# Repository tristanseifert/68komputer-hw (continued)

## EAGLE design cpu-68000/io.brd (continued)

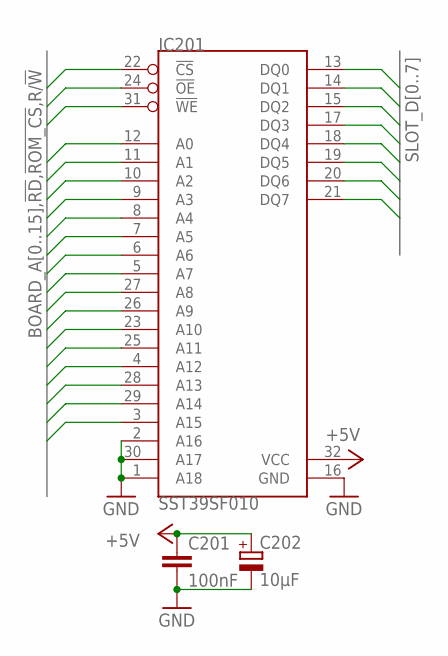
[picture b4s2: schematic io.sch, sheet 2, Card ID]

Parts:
C201: 100nF; C0805; MOUSER 710-885012207072
C202: 10µF; SMC_B; MOUSER 581-TAJB106K020RNJV
IC201: SST39SF010; PLCC-S32; MOUSER 579-SST3910A554INHET

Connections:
!RD: IC201.24 (!OE); also elsewhere on the board
!ROM_CS: IC201.22 (!CS); also elsewhere on the board
+5V: C201.1, C202.+, IC201.32 (VCC); also elsewhere on the board
BOARD_A0: IC201.12 (A0); also elsewhere on the board
BOARD_A1: IC201.11 (A1); also elsewhere on the board
BOARD_A2: IC201.10 (A2); also elsewhere on the board
BOARD_A3: IC201.9 (A3); also elsewhere on the board
BOARD_A4: IC201.8 (A4); also elsewhere on the board
BOARD_A5: IC201.7 (A5); also elsewhere on the board
BOARD_A6: IC201.6 (A6); also elsewhere on the board
BOARD_A7: IC201.5 (A7); also elsewhere on the board
BOARD_A8: IC201.27 (A8); also elsewhere on the board
BOARD_A9: IC201.26 (A9); also elsewhere on the board
BOARD_A10: IC201.23 (A10); also elsewhere on the board
BOARD_A11: IC201.25 (A11); also elsewhere on the board
BOARD_A12: IC201.4 (A12); also elsewhere on the board
BOARD_A13: IC201.28 (A13); also elsewhere on the board
BOARD_A14: IC201.29 (A14); also elsewhere on the board
BOARD_A15: IC201.3 (A15); also elsewhere on the board
GND: C201.2, C202.-, IC201.1 (A18), IC201.2 (A16), IC201.16 (GND), IC201.30 (A17); also elsewhere on the board
R/!W!: IC201.31 (!WE); also elsewhere on the board
SLOT_D0: IC201.13 (DQ0); also elsewhere on the board
SLOT_D1: IC201.14 (DQ1); also elsewhere on the board
SLOT_D2: IC201.15 (DQ2); also elsewhere on the board
SLOT_D3: IC201.17 (DQ3); also elsewhere on the board
SLOT_D4: IC201.18 (DQ4); also elsewhere on the board
SLOT_D5: IC201.19 (DQ5); also elsewhere on the board
SLOT_D6: IC201.20 (DQ6); also elsewhere on the board
SLOT_D7: IC201.21 (DQ7); also elsewhere on the board

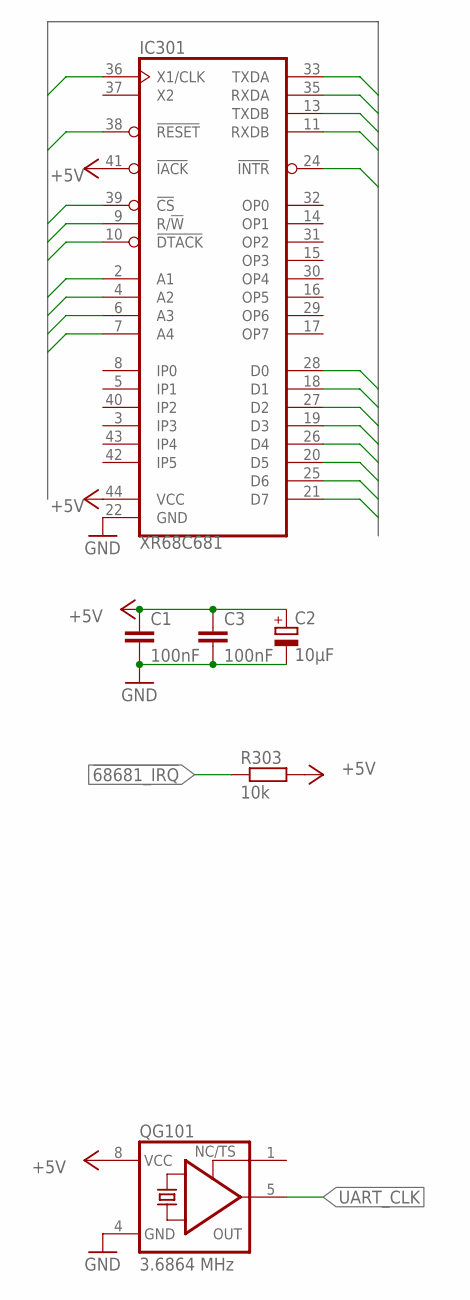
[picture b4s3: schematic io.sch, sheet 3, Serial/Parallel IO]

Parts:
C1, C3: 100nF; C0805; MOUSER 710-885012207072
C2: 10µF; SMC_B; MOUSER 581-TAJB106K020RNJV
IC301: XR68C681; PLCC-S44; MOUSER 701-XR68C681CJ-F
QG101: 3.6864 MHz; DIL08S; MOUSER 774-MXO45HS-3C-3.6
R303: 10k; R2012; MOUSER 652-CR0805FX-1002ELF

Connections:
!68681_IRQ: IC301.24 (!INTR), R303.1
!DTACK: IC301.10 (!DTACK); also elsewhere on the board
!DUART_CS: IC301.39 (!CS); also elsewhere on the board
!LWE: IC301.9 (R/!W)
!RESET: IC301.38 (!RESET); also elsewhere on the board
+5V: C1.1, C2.+, C3.1, IC301.41 (!IACK), IC301.44 (VCC), QG101.8 (VCC), R303.2; also elsewhere on the board
A_RX: IC301.35 (RXDA)
A_TX: IC301.33 (TXDA)
BOARD_A0: IC301.2 (A1); also elsewhere on the board
BOARD_A1: IC301.4 (A2); also elsewhere on the board
BOARD_A2: IC301.6 (A3); also elsewhere on the board
BOARD_A3: IC301.7 (A4); also elsewhere on the board
BOARD_D0: IC301.28 (D0); also elsewhere on the board
BOARD_D1: IC301.18 (D1); also elsewhere on the board
BOARD_D2: IC301.27 (D2); also elsewhere on the board
BOARD_D3: IC301.19 (D3); also elsewhere on the board
BOARD_D4: IC301.26 (D4); also elsewhere on the board
BOARD_D5: IC301.20 (D5); also elsewhere on the board
BOARD_D6: IC301.25 (D6); also elsewhere on the board
BOARD_D7: IC301.21 (D7); also elsewhere on the board
B_RX: IC301.11 (RXDB)
B_TX: IC301.13 (TXDB)
GND: C1.2, C2.-, C3.2, IC301.22 (GND), QG101.4 (GND); also elsewhere on the board
UART_CLK: IC301.36 (X1/CLK), QG101.5 (OUT); also elsewhere on the board

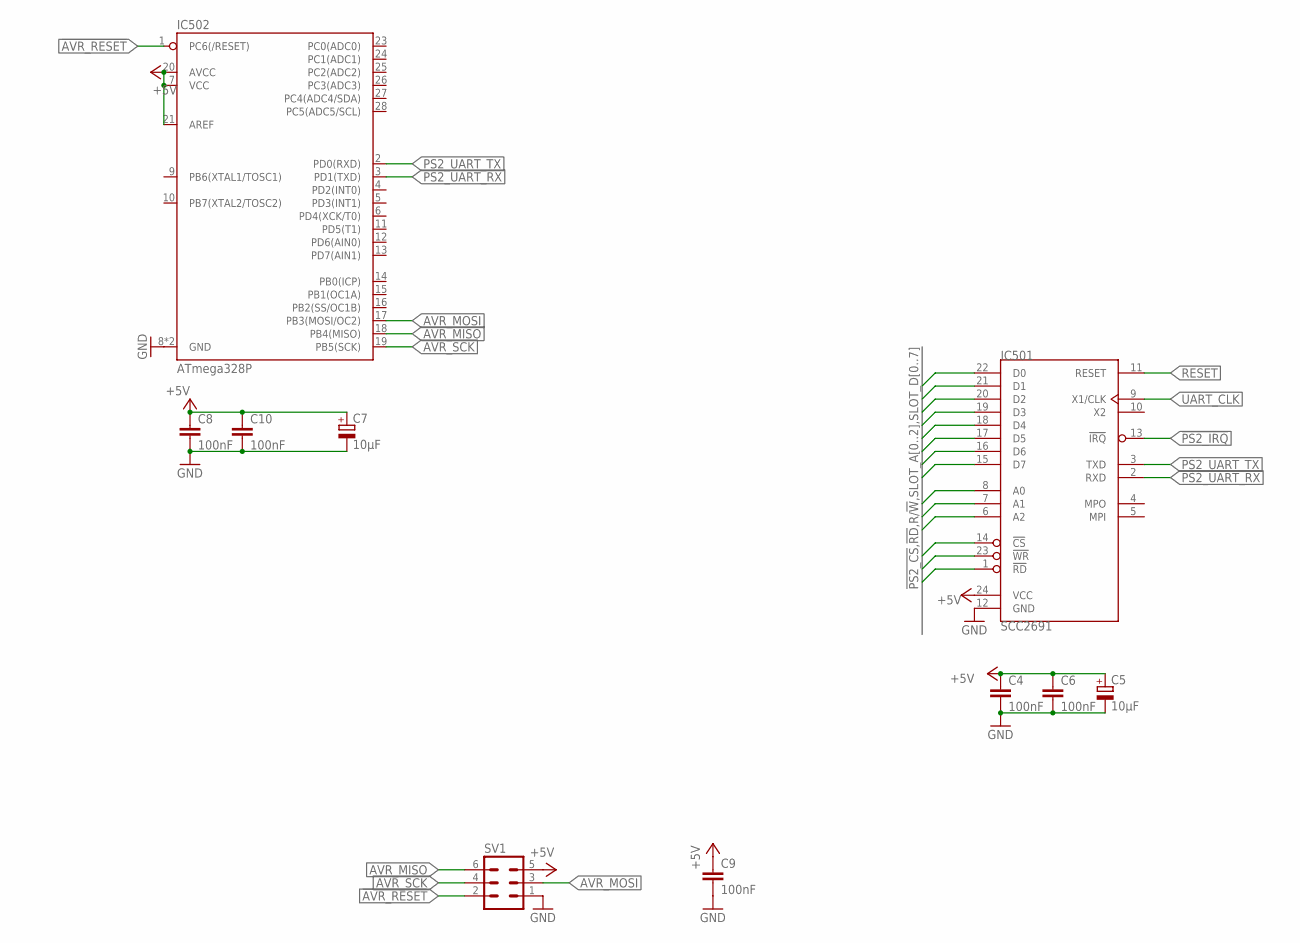
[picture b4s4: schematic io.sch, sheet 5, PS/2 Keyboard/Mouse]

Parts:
C4, C6, C8, C9, C10: 100nF; C0805; MOUSER 710-885012207072
C5, C7: 10µF; SMC_B; MOUSER 581-TAJB106K020RNJV
IC501: SCC2691; DIL24S; MOUSER_SOCKET 575-1104732441001000
IC502: ATmega328P; DIP28; MOUSER 556-ATMEGA328-PU
SV1: ML6

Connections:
!AVR_RESET: IC502.1 (PC6(/RESET)), SV1.2
!PS2_CS: IC501.14 (!CS); also elsewhere on the board
!PS2_IRQ: IC501.13 (!IRQ)
!RD: IC501.1 (!RD); also elsewhere on the board
+5V: C4.1, C5.+, C6.1, C7.+, C8.1, C9.1, C10.1, IC501.24 (VCC), IC502.7 (VCC), IC502.20 (AVCC), IC502.21 (AREF), SV1.5; also elsewhere on the board
AVR_MISO: IC502.18 (PB4(MISO)), SV1.6
AVR_MOSI: IC502.17 (PB3(MOSI/OC2)), SV1.3
AVR_SCK: IC502.19 (PB5(SCK)), SV1.4
GND: C4.2, C5.-, C6.2, C7.-, C8.2, C9.2, C10.2, IC501.12 (GND), IC502.8 (GND), IC502.22 (GND), SV1.1; also elsewhere on the board
PS2_UART_RX: IC501.2 (RXD), IC502.3 (PD1(TXD))
PS2_UART_TX: IC501.3 (TXD), IC502.2 (PD0(RXD))
R/!W!: IC501.23 (!WR); also elsewhere on the board
RESET: IC501.11 (RESET)
SLOT_A0: IC501.8 (A0)
SLOT_A1: IC501.7 (A1)
SLOT_A2: IC501.6 (A2)
SLOT_D0: IC501.22 (D0); also elsewhere on the board
SLOT_D1: IC501.21 (D1); also elsewhere on the board
SLOT_D2: IC501.20 (D2); also elsewhere on the board
SLOT_D3: IC501.19 (D3); also elsewhere on the board
SLOT_D4: IC501.18 (D4); also elsewhere on the board
SLOT_D5: IC501.17 (D5); also elsewhere on the board
SLOT_D6: IC501.16 (D6); also elsewhere on the board
SLOT_D7: IC501.15 (D7); also elsewhere on the board
UART_CLK: IC501.9 (X1/CLK); also elsewhere on the board

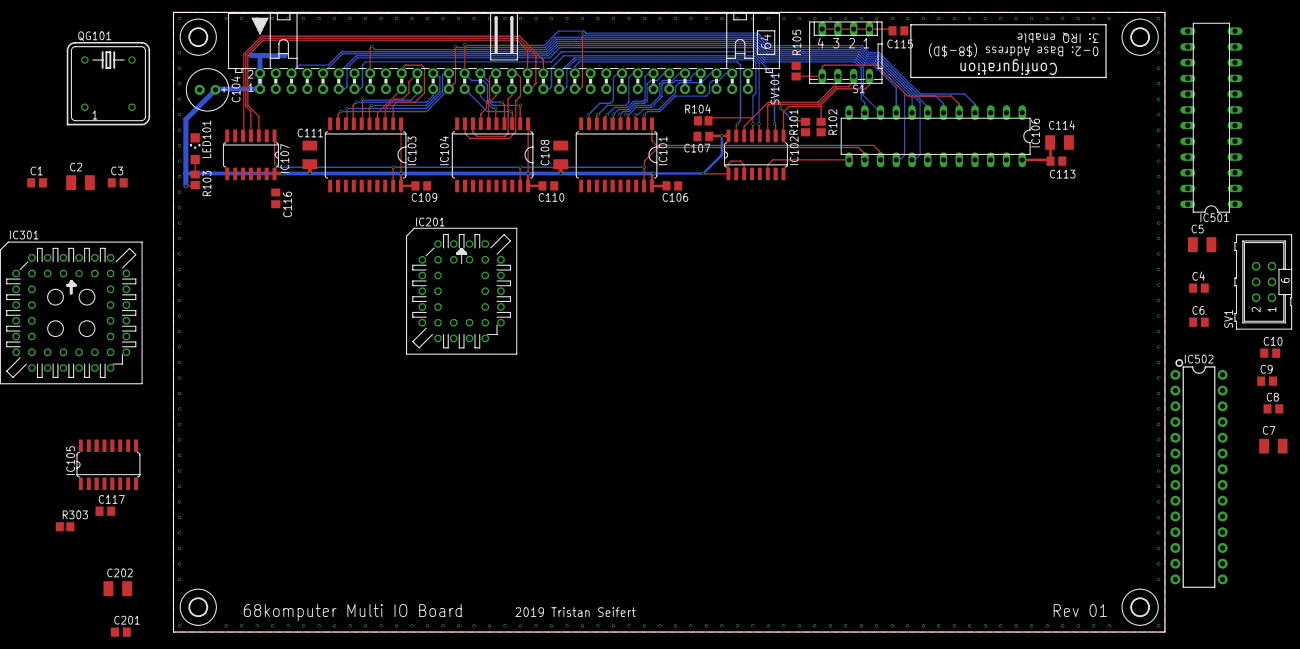
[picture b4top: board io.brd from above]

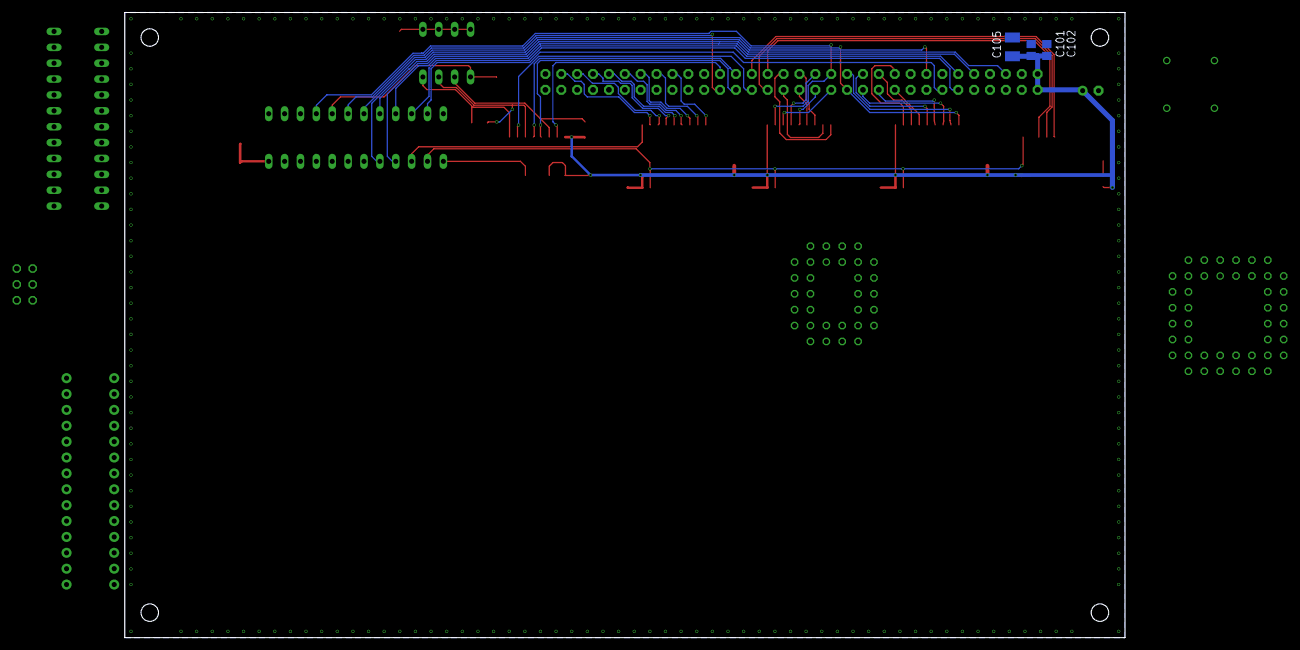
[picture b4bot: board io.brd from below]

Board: 2 copper layers, 160.0 x 100.0 mm, 53 parts (3 on the bottom side), 92 nets.

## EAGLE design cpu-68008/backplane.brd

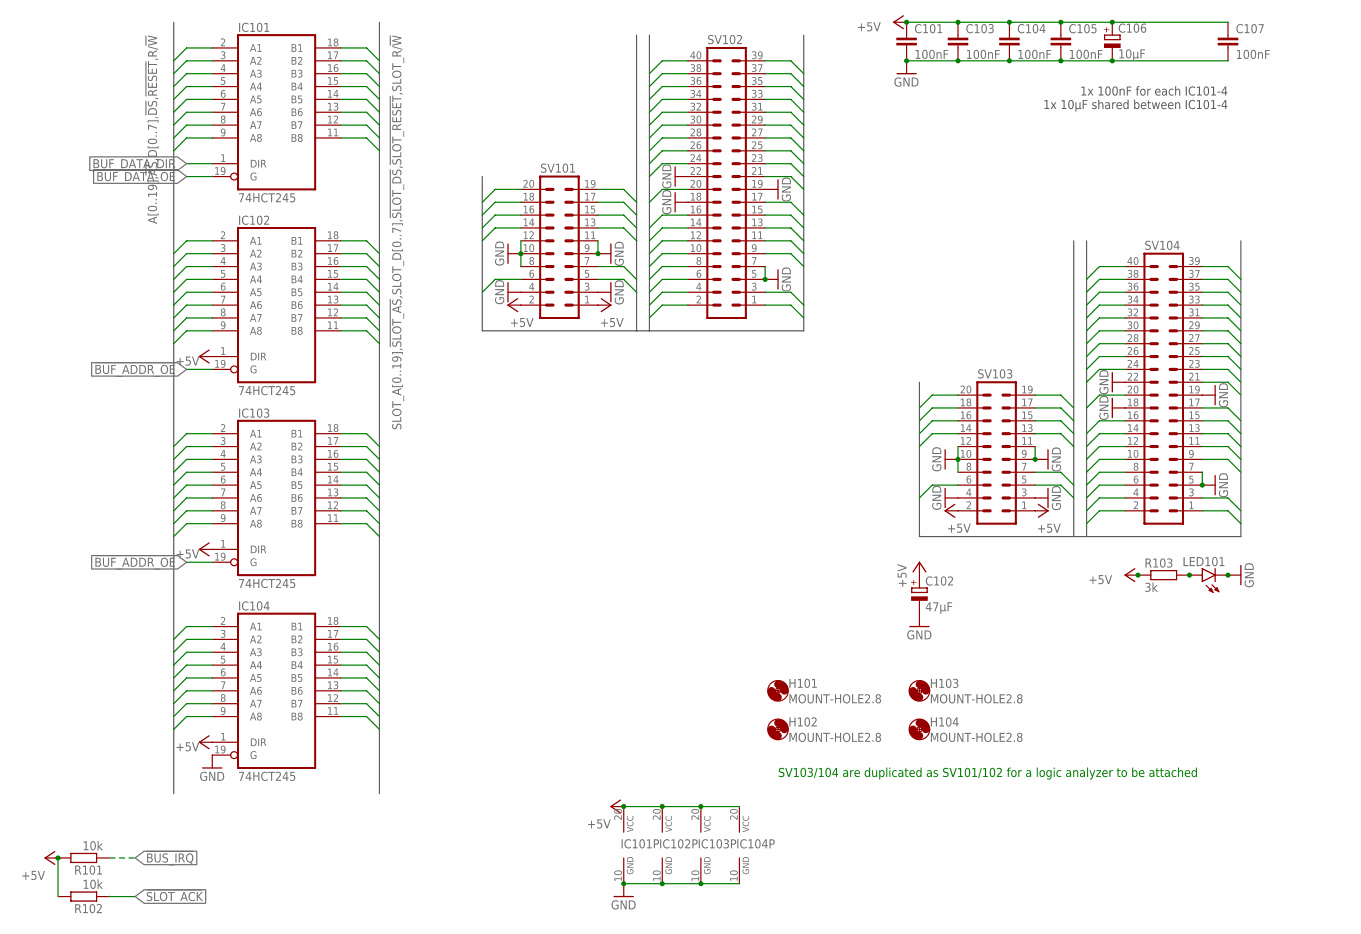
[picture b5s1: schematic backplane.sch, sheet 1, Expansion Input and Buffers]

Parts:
C101, C103, C104, C105, C107: 100nF; C0805; MOUSER 710-885012207072
C102: 47µF; E2-5; MOUSER 710-860020472006
C106: 10µF; SMC_B; MOUSER 581-TAJB106K020RNJV
H101, H102, H103, H104: MOUNT-HOLE2.8; 2,8
IC101, IC102, IC103, IC104: 74HCT245; SO20W
LED101: LEDCHIPLED_1206; CHIPLED_1206; MOUSER 710-156120YS75300
R101, R102: 10k; R2012; MOUSER 652-CR0805FX-1002ELF
R103: 3k; R2012; MOUSER 652-CR0805JW-302ELF
SV101: MA10-2
SV102: MA20-2
SV103: MA10-2W
SV104: MA20-2W

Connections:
!AS: IC104.2 (A1), SV102.33, SV104.33
!BERR: SV102.9, SV104.9
!BG: SV102.25, SV104.25
!BR: SV102.23, SV104.23
!BUF_ADDR_OE: IC102.19 (G), IC103.19 (G); also elsewhere on the board
!BUF_DATA_OE: IC101.19 (G); also elsewhere on the board
!BUS_CS: SV101.7, SV103.7; also elsewhere on the board
!BUS_DTACK: SV101.6, SV103.6; also elsewhere on the board
!BUS_IRQ: R101.1, SV101.5, SV103.5; also elsewhere on the board
!DS: IC104.3 (A2), SV102.31, SV104.31
!DTACK: SV102.27, SV104.27
!HALT: SV102.17, SV104.17
!RESET: IC104.9 (A8), SV102.15, SV104.15
!SLOT_ACK: R102.1; also elsewhere on the board
!SLOT_AS: IC104.18 (B1); also elsewhere on the board
!SLOT_RESET: IC104.11 (B8); also elsewhere on the board
!VPA: SV102.11, SV104.11
+5V: C101.1, C102.+, C103.1, C104.1, C105.1, C106.+, C107.1, IC101.20 (VCC), IC102.1 (DIR), IC102.20 (VCC), IC103.1 (DIR), IC103.20 (VCC), IC104.1 (DIR), IC104.20 (VCC), R101.2, R102.2, R103.1, SV101.1, SV101.2, SV103.1, SV103.2; also elsewhere on the board
A0: IC102.5 (A4), SV101.17, SV103.17
A1: IC102.7 (A6), SV101.15, SV103.15
A2: IC102.9 (A8), SV101.13, SV103.13
A3: IC102.8 (A7), SV101.14, SV103.14
A4: IC102.6 (A5), SV101.16, SV103.16
A5: IC102.4 (A3), SV101.18, SV103.18
A6: IC102.3 (A2), SV101.20, SV103.20
A7: IC102.2 (A1), SV102.2, SV104.2
A8: IC103.9 (A8), SV102.4, SV104.4
A9: IC103.8 (A7), SV102.6, SV104.6
A10: IC103.7 (A6), SV102.8, SV104.8
A11: IC103.6 (A5), SV102.10, SV104.10
A12: IC103.5 (A4), SV102.12, SV104.12
A13: IC103.4 (A3), SV102.14, SV104.14
A14: IC103.3 (A2), SV102.16, SV104.16
A15: IC103.2 (A1), SV102.20, SV104.20
A16: IC104.8 (A7), SV102.24, SV104.24
A17: IC104.7 (A6), SV102.26, SV104.26
A18: IC104.6 (A5), SV102.28, SV104.28
A19: IC104.4 (A3), SV102.30, SV104.30
BUF_DATA_DIR: IC101.1 (DIR); also elsewhere on the board
CLK: SV102.21, SV104.21; also elsewhere on the board
D0: IC101.7 (A6), SV102.35, SV104.35
D1: IC101.5 (A4), SV102.37, SV104.37
D2: IC101.3 (A2), SV102.39, SV104.39
D3: IC101.2 (A1), SV102.40, SV104.40
D4: IC101.4 (A3), SV102.38, SV104.38
D5: IC101.6 (A5), SV102.36, SV104.36
D6: IC101.8 (A7), SV102.34, SV104.34
D7: IC101.9 (A8), SV102.32, SV104.32
E: SV102.13, SV104.13
FC0: SV101.19, SV103.19
FC1: SV102.1, SV104.1
FC2: SV102.3, SV104.3
GND: C101.2, C102.-, C103.2, C104.2, C105.2, C106.-, C107.2, IC101.10 (GND), IC102.10 (GND), IC103.10 (GND), IC104.10 (GND), IC104.19 (G), LED101.C, SV101.3, SV101.4, SV101.8, SV101.9, SV101.10, SV101.11, SV101.12, SV102.5, SV102.7, SV102.18, SV102.19, SV102.22, SV103.3, SV103.4, SV103.8, SV103.9, SV103.10, SV103.11, SV103.12, SV104.5, SV104.7, SV104.18, SV104.19, SV104.22; also elsewhere on the board
unnamed: LED101.A, R103.2
R/!W!: IC104.5 (A4), SV102.29, SV104.29
SLOT_A0: IC102.15 (B4); also elsewhere on the board
SLOT_A1: IC102.13 (B6); also elsewhere on the board
SLOT_A2: IC102.11 (B8); also elsewhere on the board
SLOT_A3: IC102.12 (B7); also elsewhere on the board
SLOT_A4: IC102.14 (B5); also elsewhere on the board
SLOT_A5: IC102.16 (B3); also elsewhere on the board
SLOT_A6: IC102.17 (B2); also elsewhere on the board
SLOT_A7: IC102.18 (B1); also elsewhere on the board
SLOT_A8: IC103.11 (B8); also elsewhere on the board
SLOT_A9: IC103.12 (B7); also elsewhere on the board
SLOT_A10: IC103.13 (B6); also elsewhere on the board
SLOT_A11: IC103.14 (B5); also elsewhere on the board
SLOT_A12: IC103.15 (B4); also elsewhere on the board
SLOT_A13: IC103.16 (B3); also elsewhere on the board
SLOT_A14: IC103.17 (B2); also elsewhere on the board
SLOT_A15: IC103.18 (B1); also elsewhere on the board
SLOT_A16: IC104.12 (B7); also elsewhere on the board
SLOT_A17: IC104.13 (B6); also elsewhere on the board
SLOT_A18: IC104.14 (B5); also elsewhere on the board
SLOT_A19: IC104.16 (B3); also elsewhere on the board
SLOT_D0: IC101.13 (B6); also elsewhere on the board
SLOT_D1: IC101.15 (B4); also elsewhere on the board
SLOT_D2: IC101.17 (B2); also elsewhere on the board
SLOT_D3: IC101.18 (B1); also elsewhere on the board
SLOT_D4: IC101.16 (B3); also elsewhere on the board
SLOT_D5: IC101.14 (B5); also elsewhere on the board
SLOT_D6: IC101.12 (B7); also elsewhere on the board
SLOT_D7: IC101.11 (B8); also elsewhere on the board
SLOT_R/!W!: IC104.15 (B4); also elsewhere on the board

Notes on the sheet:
1x 100nF for each IC101-4 1x 10µF shared between IC101-4
SV103/104 are duplicated as SV101/102 for a logic analyzer to be attached

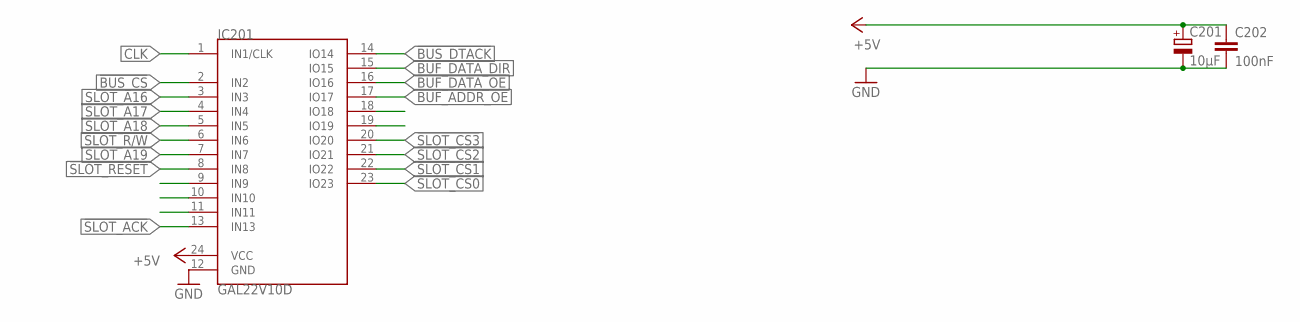
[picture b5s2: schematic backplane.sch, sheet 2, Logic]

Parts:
C201: 10µF; SMC_B; MOUSER 581-TAJB106K020RNJV
C202: 100nF; C0805; MOUSER 710-885012207072
IC201: GAL22V10D; DIL24S

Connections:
!BUF_ADDR_OE: IC201.17 (IO17); also elsewhere on the board
!BUF_DATA_OE: IC201.16 (IO16); also elsewhere on the board
!BUS_CS: IC201.2 (IN2); also elsewhere on the board
!BUS_DTACK: IC201.14 (IO14); also elsewhere on the board
!SLOT_ACK: IC201.13 (IN13); also elsewhere on the board
!SLOT_CS0: IC201.23 (IO23); also elsewhere on the board
!SLOT_CS1: IC201.22 (IO22); also elsewhere on the board
!SLOT_CS2: IC201.21 (IO21); also elsewhere on the board
!SLOT_CS3: IC201.20 (IO20); also elsewhere on the board
!SLOT_RESET: IC201.8 (IN8); also elsewhere on the board
+5V: C201.+, C202.1, IC201.24 (VCC); also elsewhere on the board
BUF_DATA_DIR: IC201.15 (IO15); also elsewhere on the board
CLK: IC201.1 (IN1/CLK); also elsewhere on the board
GND: C201.-, C202.2, IC201.12 (GND); also elsewhere on the board
SLOT_A16: IC201.3 (IN3); also elsewhere on the board
SLOT_A17: IC201.4 (IN4); also elsewhere on the board
SLOT_A18: IC201.5 (IN5); also elsewhere on the board
SLOT_A19: IC201.7 (IN7); also elsewhere on the board
SLOT_R/!W!: IC201.6 (IN6); also elsewhere on the board

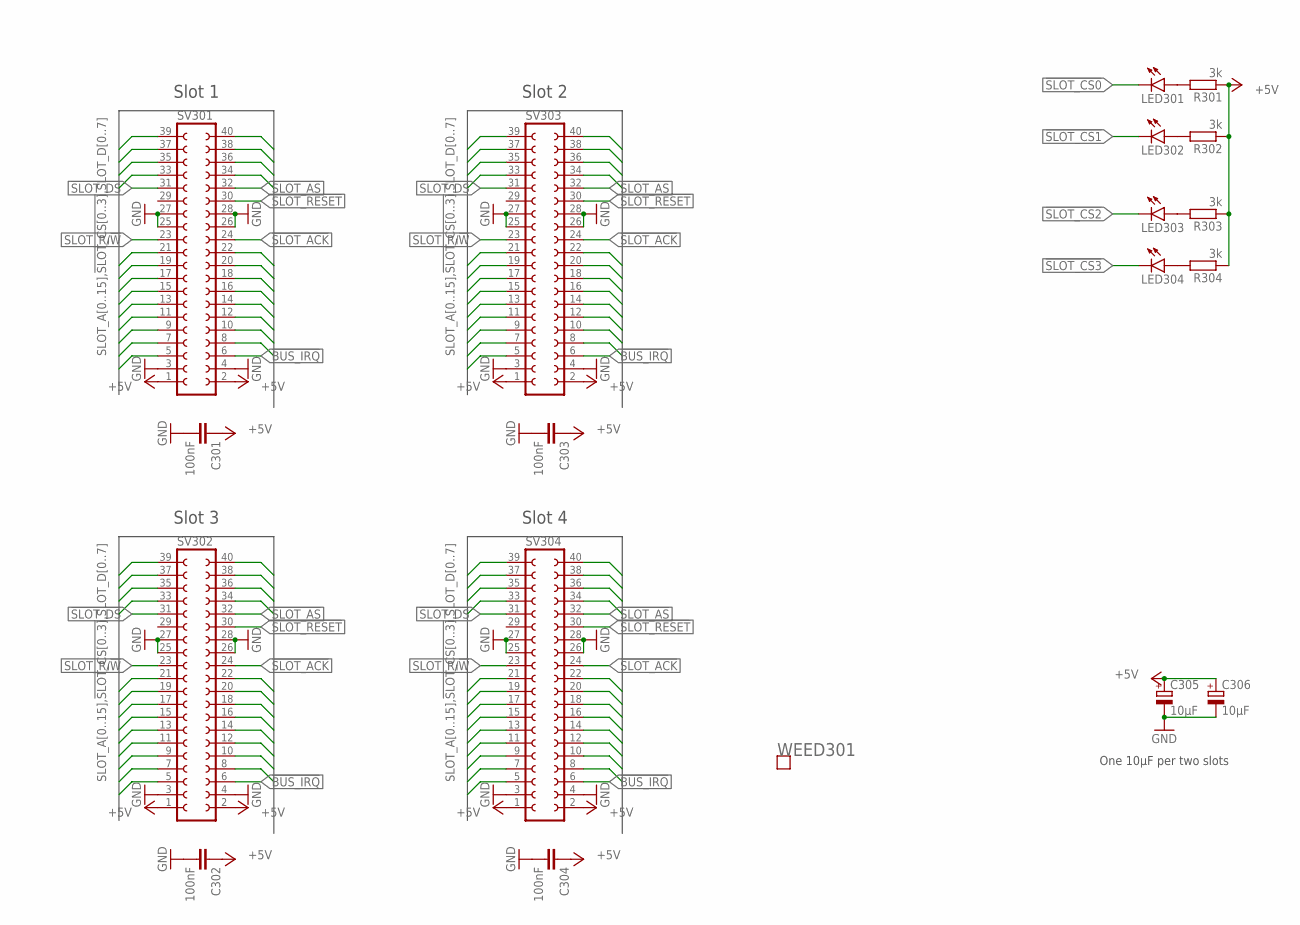
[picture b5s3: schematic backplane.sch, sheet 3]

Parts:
C301, C302, C303, C304: 100nF; C0805; MOUSER 710-885012207072
C305, C306: 10µF; SMC_B; MOUSER 581-TAJB106K020RNJV
LED301, LED302, LED303, LED304: LEDCHIPLED_1206; CHIPLED_1206; MOUSER 710-156120VS75300
R301, R302, R303, R304: 3k; R2012; MOUSER 652-CR0805JW-302ELF
SV301, SV302, SV303, SV304: FE20-2
WEED301: WEED; DOINK

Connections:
!BUS_IRQ: SV301.6, SV302.6, SV303.6, SV304.6; also elsewhere on the board
!SLOT_ACK: SV301.24, SV302.24, SV303.24, SV304.24; also elsewhere on the board
!SLOT_AS: SV301.32, SV302.32, SV303.32, SV304.32; also elsewhere on the board
!SLOT_CS0: LED301.C, SV301.5; also elsewhere on the board
!SLOT_CS1: LED302.C, SV303.5; also elsewhere on the board
!SLOT_CS2: LED303.C, SV302.5; also elsewhere on the board
!SLOT_CS3: LED304.C, SV304.5; also elsewhere on the board
!SLOT_RESET: SV301.30, SV302.30, SV303.30, SV304.30; also elsewhere on the board
+5V: C301.1, C302.1, C303.1, C304.1, C305.+, C306.+, R301.1, R302.1, R303.1, R304.1, SV301.1, SV301.2, SV302.1, SV302.2, SV303.1, SV303.2, SV304.1, SV304.2; also elsewhere on the board
GND: C301.2, C302.2, C303.2, C304.2, C305.-, C306.-, SV301.3, SV301.4, SV301.25, SV301.26, SV301.27, SV301.28, SV302.3, SV302.4, SV302.25, SV302.26, SV302.27, SV302.28, SV303.3, SV303.4, SV303.25, SV303.26, SV303.27, SV303.28, SV304.3, SV304.4, SV304.25, SV304.26, SV304.27, SV304.28; also elsewhere on the board
unnamed: LED302.A, R302.2
unnamed: LED301.A, R301.2
unnamed: LED304.A, R304.2
unnamed: LED303.A, R303.2
SLOT_A0: SV301.12, SV302.12, SV303.12, SV304.12; also elsewhere on the board
SLOT_A1: SV301.10, SV302.10, SV303.10, SV304.10; also elsewhere on the board
SLOT_A2: SV301.8, SV302.8, SV303.8, SV304.8; also elsewhere on the board
SLOT_A3: SV301.7, SV302.7, SV303.7, SV304.7; also elsewhere on the board
SLOT_A4: SV301.9, SV302.9, SV303.9, SV304.9; also elsewhere on the board
SLOT_A5: SV301.11, SV302.11, SV303.11, SV304.11; also elsewhere on the board
SLOT_A6: SV301.14, SV302.14, SV303.14, SV304.14; also elsewhere on the board
SLOT_A7: SV301.13, SV302.13, SV303.13, SV304.13; also elsewhere on the board
SLOT_A8: SV301.16, SV302.16, SV303.16, SV304.16; also elsewhere on the board
SLOT_A9: SV301.15, SV302.15, SV303.15, SV304.15; also elsewhere on the board
SLOT_A10: SV301.18, SV302.18, SV303.18, SV304.18; also elsewhere on the board
SLOT_A11: SV301.17, SV302.17, SV303.17, SV304.17; also elsewhere on the board
SLOT_A12: SV301.20, SV302.20, SV303.20, SV304.20; also elsewhere on the board
SLOT_A13: SV301.19, SV302.19, SV303.19, SV304.19; also elsewhere on the board
SLOT_A14: SV301.22, SV302.22, SV303.22, SV304.22; also elsewhere on the board
SLOT_A15: SV301.21, SV302.21, SV303.21, SV304.21; also elsewhere on the board
SLOT_D0: SV301.35, SV302.35, SV303.35, SV304.35; also elsewhere on the board
SLOT_D1: SV301.37, SV302.37, SV303.37, SV304.37; also elsewhere on the board
SLOT_D2: SV301.39, SV302.39, SV303.39, SV304.39; also elsewhere on the board
SLOT_D3: SV301.40, SV302.40, SV303.40, SV304.40; also elsewhere on the board
SLOT_D4: SV301.38, SV302.38, SV303.38, SV304.38; also elsewhere on the board
SLOT_D5: SV301.36, SV302.36, SV303.36, SV304.36; also elsewhere on the board
SLOT_D6: SV301.34, SV302.34, SV303.34, SV304.34; also elsewhere on the board
SLOT_D7: SV301.33, SV302.33, SV303.33, SV304.33; also elsewhere on the board
SLOT_R/!W!: SV301.23, SV302.23, SV303.23, SV304.23; also elsewhere on the board

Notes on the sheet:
Slot 1
Slot 2
Slot 3
Slot 4
One 10µF per two slots

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
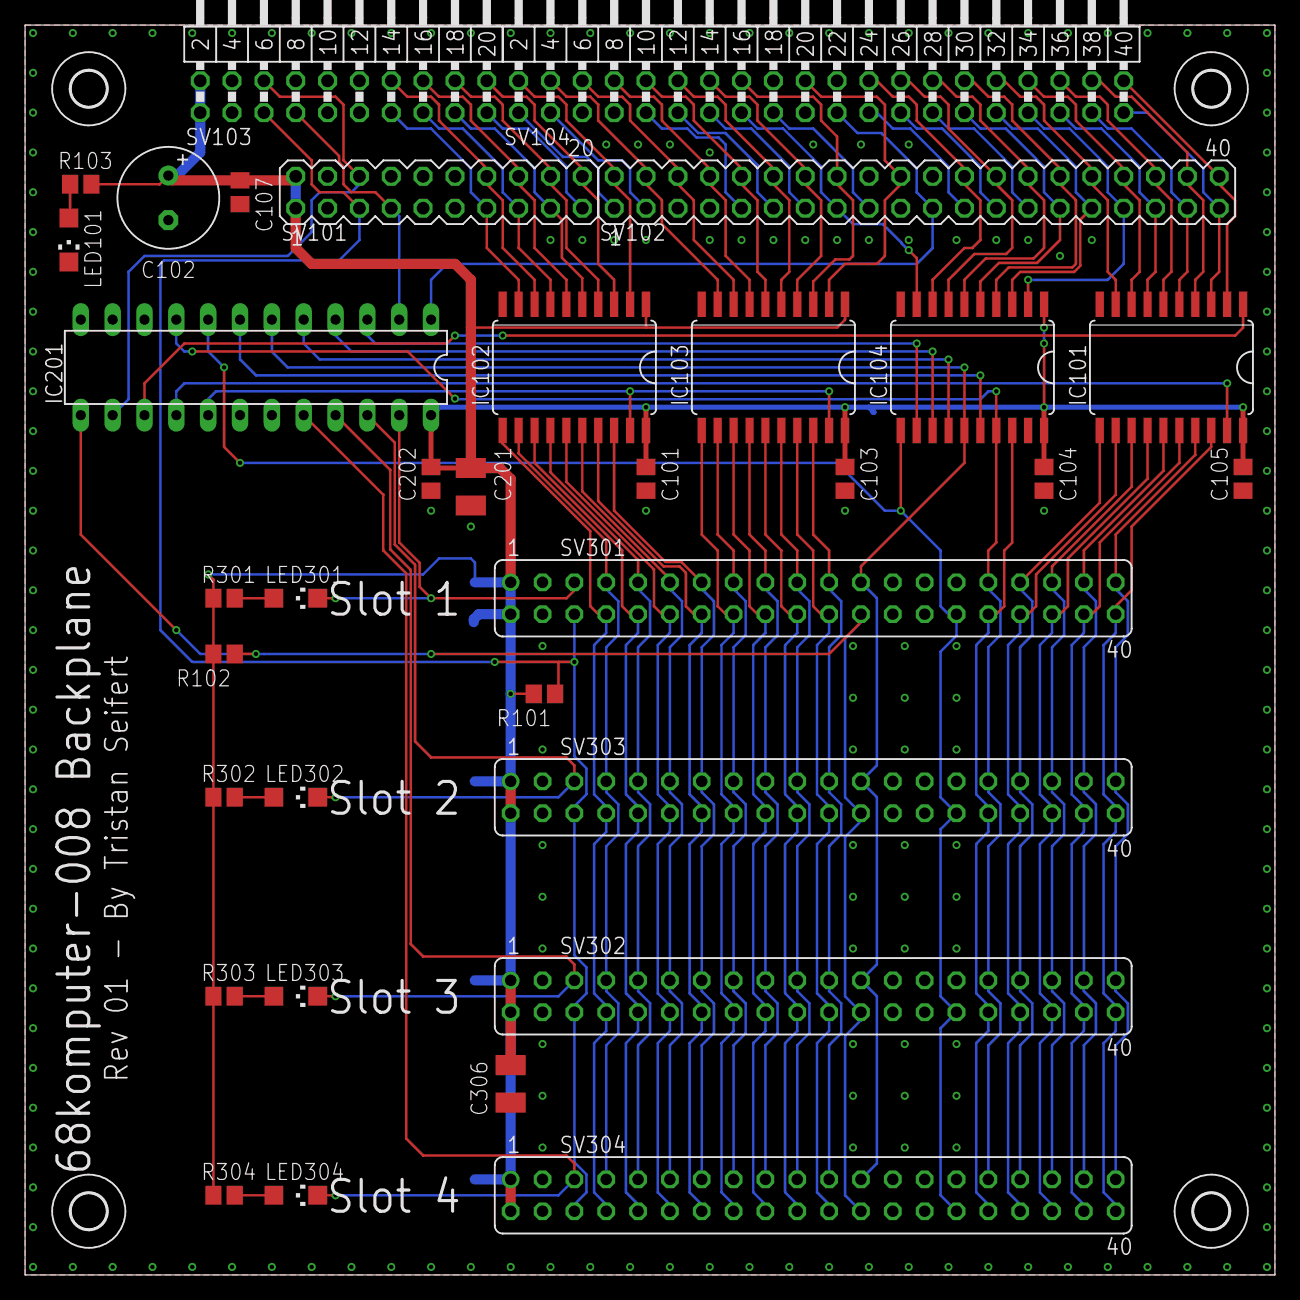
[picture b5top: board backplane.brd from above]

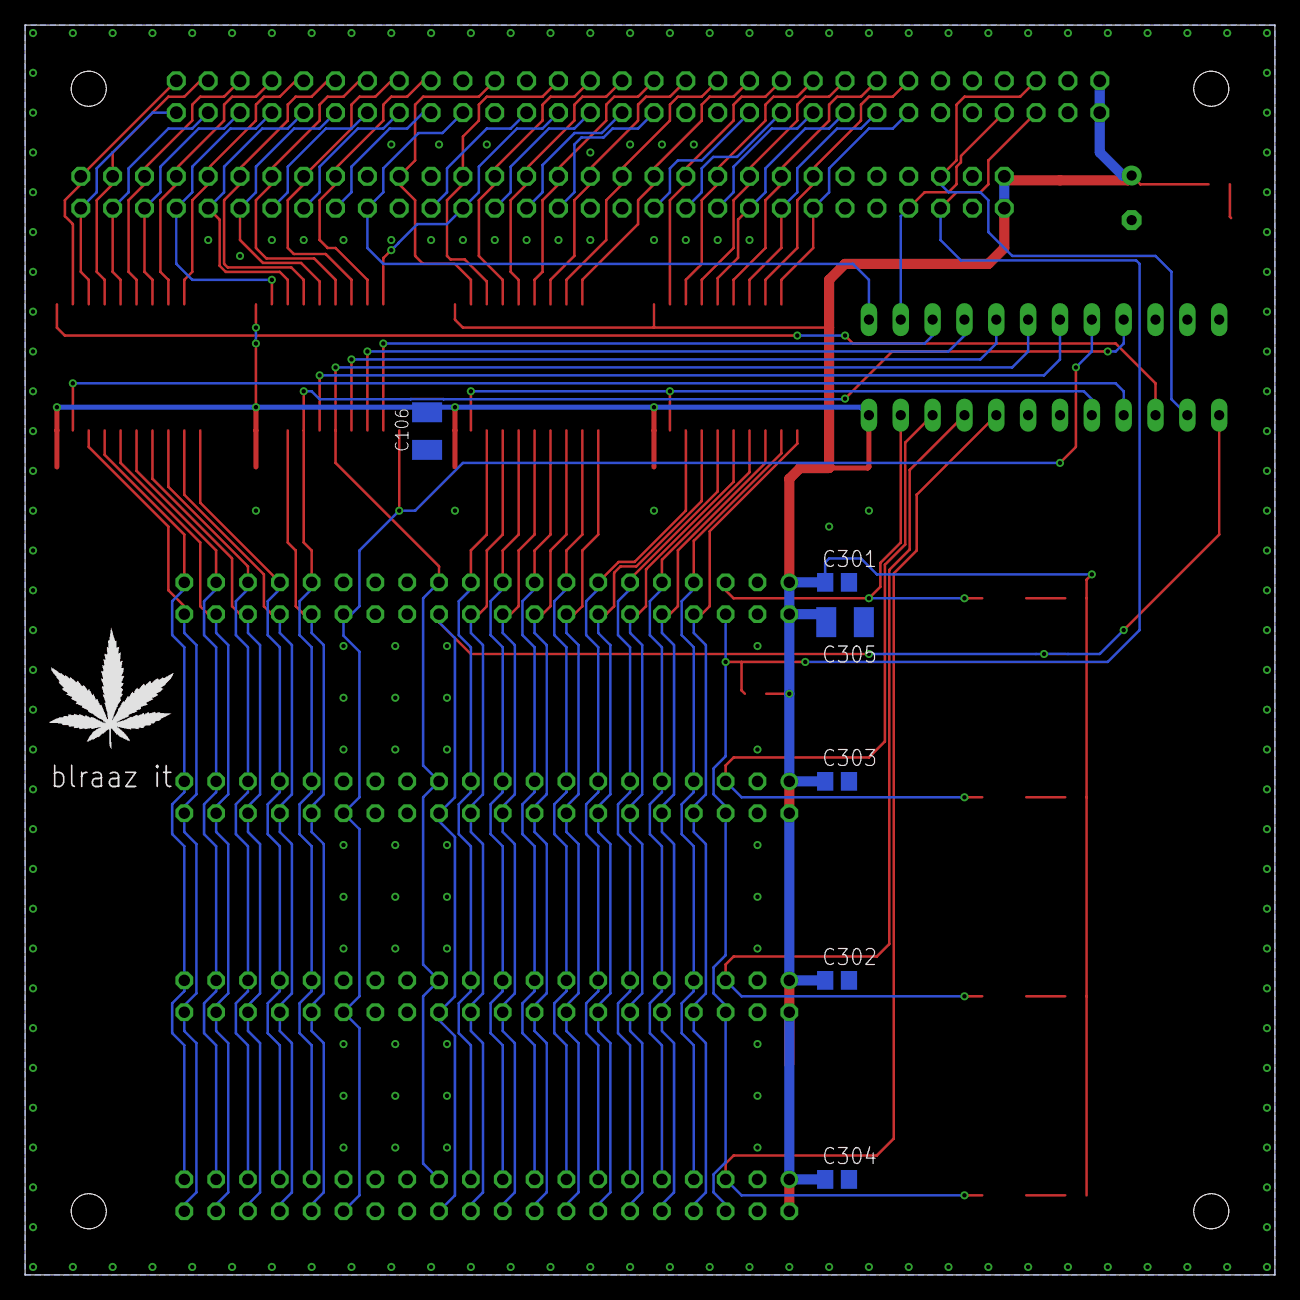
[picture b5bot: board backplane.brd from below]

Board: 2 copper layers, 99.7 x 99.7 mm, 45 parts (7 on the bottom side), 93 nets.

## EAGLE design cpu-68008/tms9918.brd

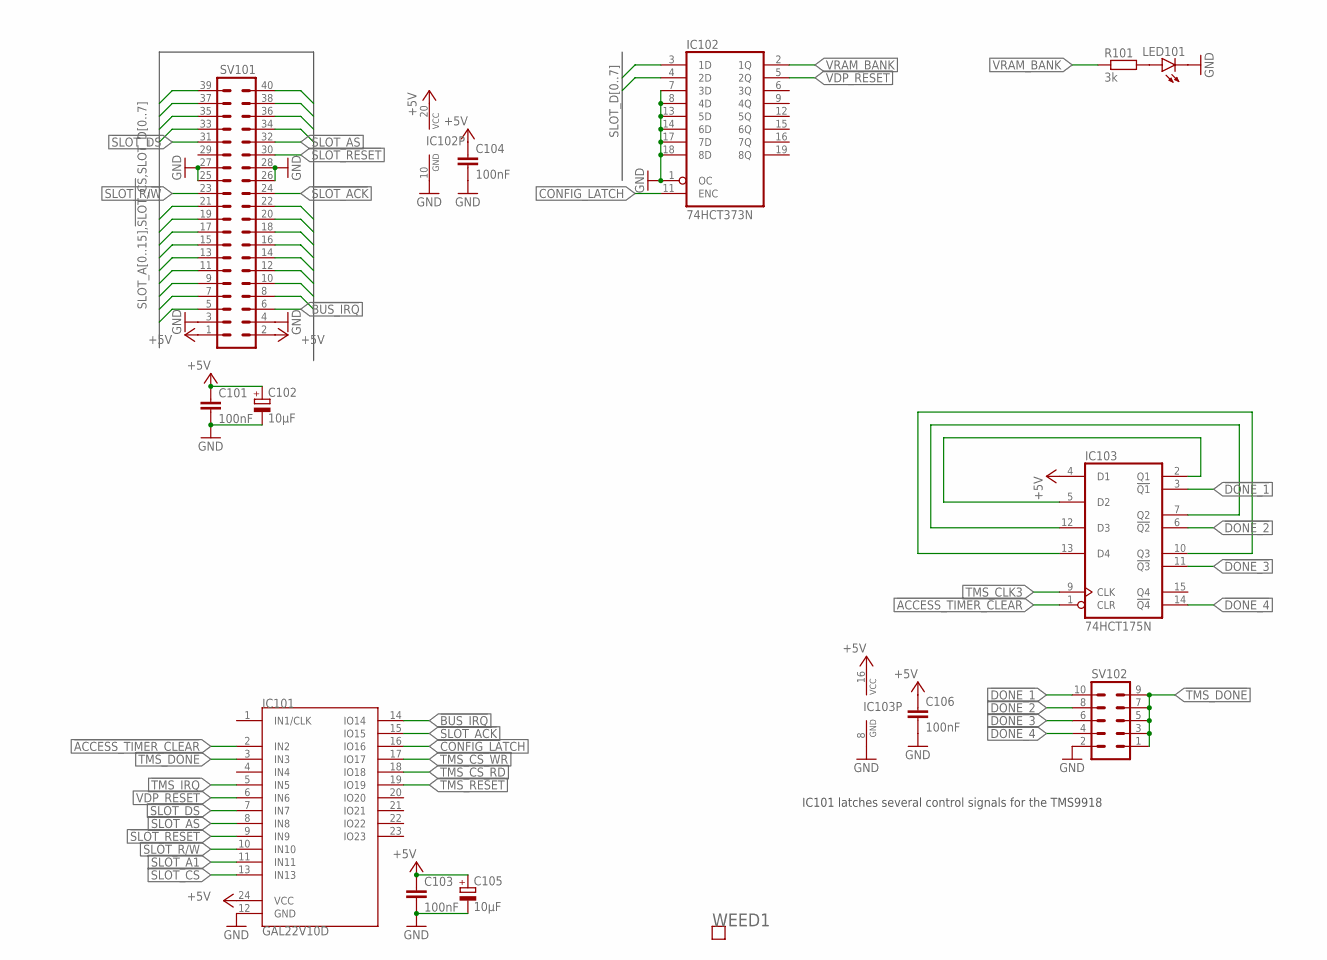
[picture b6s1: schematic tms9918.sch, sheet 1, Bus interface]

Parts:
C101, C103, C104, C106: 100nF; C0805; MOUSER 710-885012207072
C102, C105: 10µF; SMC_B; MOUSER 581-TAJB106K020RNJV
IC101: GAL22V10D; DIL24S; MOUSER_SOCKET 575-11044324
IC102: 74HCT373N; DIL20; MOUSER 595-SN74HCT373N
IC103: 74HCT175N; DIL16; MOUSER 595-CD74HCT175E
LED101: LEDCHIPLED_1206; CHIPLED_1206; MOUSER 710-156120VS75300
R101: 3k; R2012; MOUSER 652-CR0805JW-302ELF
SV101: MA20-2W
SV102: MA05-2
WEED1: WEED; DOINK

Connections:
!ACCESS_TIMER_CLEAR: IC101.2 (IN2), IC103.1 (CLR)
!BUS_IRQ: IC101.14 (IO14), SV101.6
!DONE_1: IC103.3 (!Q1), SV102.10
!DONE_2: IC103.6 (!Q2), SV102.8
!DONE_3: IC103.11 (!Q3), SV102.6
!DONE_4: IC103.14 (!Q4), SV102.4
!SLOT_ACK: IC101.15 (IO15), SV101.24
!SLOT_AS: IC101.8 (IN8), SV101.32
!SLOT_CS: IC101.13 (IN13), SV101.5
!SLOT_DS: IC101.7 (IN7), SV101.31
!SLOT_RESET: IC101.9 (IN9), SV101.30
!TMS_CS_RD: IC101.18 (IO18); also elsewhere on the board
!TMS_CS_WR: IC101.17 (IO17); also elsewhere on the board
!TMS_DONE: IC101.3 (IN3), SV102.1, SV102.3, SV102.5, SV102.7, SV102.9
!TMS_IRQ: IC101.5 (IN5); also elsewhere on the board
!TMS_RESET: IC101.19 (IO19); also elsewhere on the board
+5V: C101.1, C102.+, C103.1, C104.1, C105.+, C106.1, IC101.24 (VCC), IC102.20 (VCC), IC103.4 (D1), IC103.16 (VCC), SV101.1, SV101.2; also elsewhere on the board
CONFIG_LATCH: IC101.16 (IO16), IC102.11 (ENC)
GND: C101.2, C102.-, C103.2, C104.2, C105.-, C106.2, IC101.12 (GND), IC102.1 (OC), IC102.7 (3D), IC102.8 (4D), IC102.10 (GND), IC102.13 (5D), IC102.14 (6D), IC102.17 (7D), IC102.18 (8D), IC103.8 (GND), LED101.C, SV101.3, SV101.4, SV101.25, SV101.26, SV101.27, SV101.28, SV102.2; also elsewhere on the board
unnamed: IC103.2 (Q1), IC103.5 (D2)
unnamed: IC103.7 (Q2), IC103.12 (D3)
unnamed: IC103.10 (Q3), IC103.13 (D4)
unnamed: LED101.A, R101.2
SLOT_A0: SV101.12; also elsewhere on the board
SLOT_A1: IC101.11 (IN11), SV101.10
SLOT_A2: SV101.8
SLOT_A3: SV101.7
SLOT_A4: SV101.9
SLOT_A5: SV101.11
SLOT_A6: SV101.14
SLOT_A7: SV101.13
SLOT_A8: SV101.16
SLOT_A9: SV101.15
SLOT_A10: SV101.18
SLOT_A11: SV101.17
SLOT_A12: SV101.20
SLOT_A13: SV101.19
SLOT_A14: SV101.22
SLOT_A15: SV101.21
SLOT_D0: IC102.3 (1D), SV101.35; also elsewhere on the board
SLOT_D1: IC102.4 (2D), SV101.37; also elsewhere on the board
SLOT_D2: SV101.39; also elsewhere on the board
SLOT_D3: SV101.40; also elsewhere on the board
SLOT_D4: SV101.38; also elsewhere on the board
SLOT_D5: SV101.36; also elsewhere on the board
SLOT_D6: SV101.34; also elsewhere on the board
SLOT_D7: SV101.33; also elsewhere on the board
SLOT_R/!W!: IC101.10 (IN10), SV101.23
TMS_CLK3: IC103.9 (CLK); also elsewhere on the board
VDP_RESET: IC101.6 (IN6), IC102.5 (2Q)
VRAM_BANK: IC102.2 (1Q), R101.1; also elsewhere on the board

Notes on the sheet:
IC101 latches several control signals for the TMS9918
